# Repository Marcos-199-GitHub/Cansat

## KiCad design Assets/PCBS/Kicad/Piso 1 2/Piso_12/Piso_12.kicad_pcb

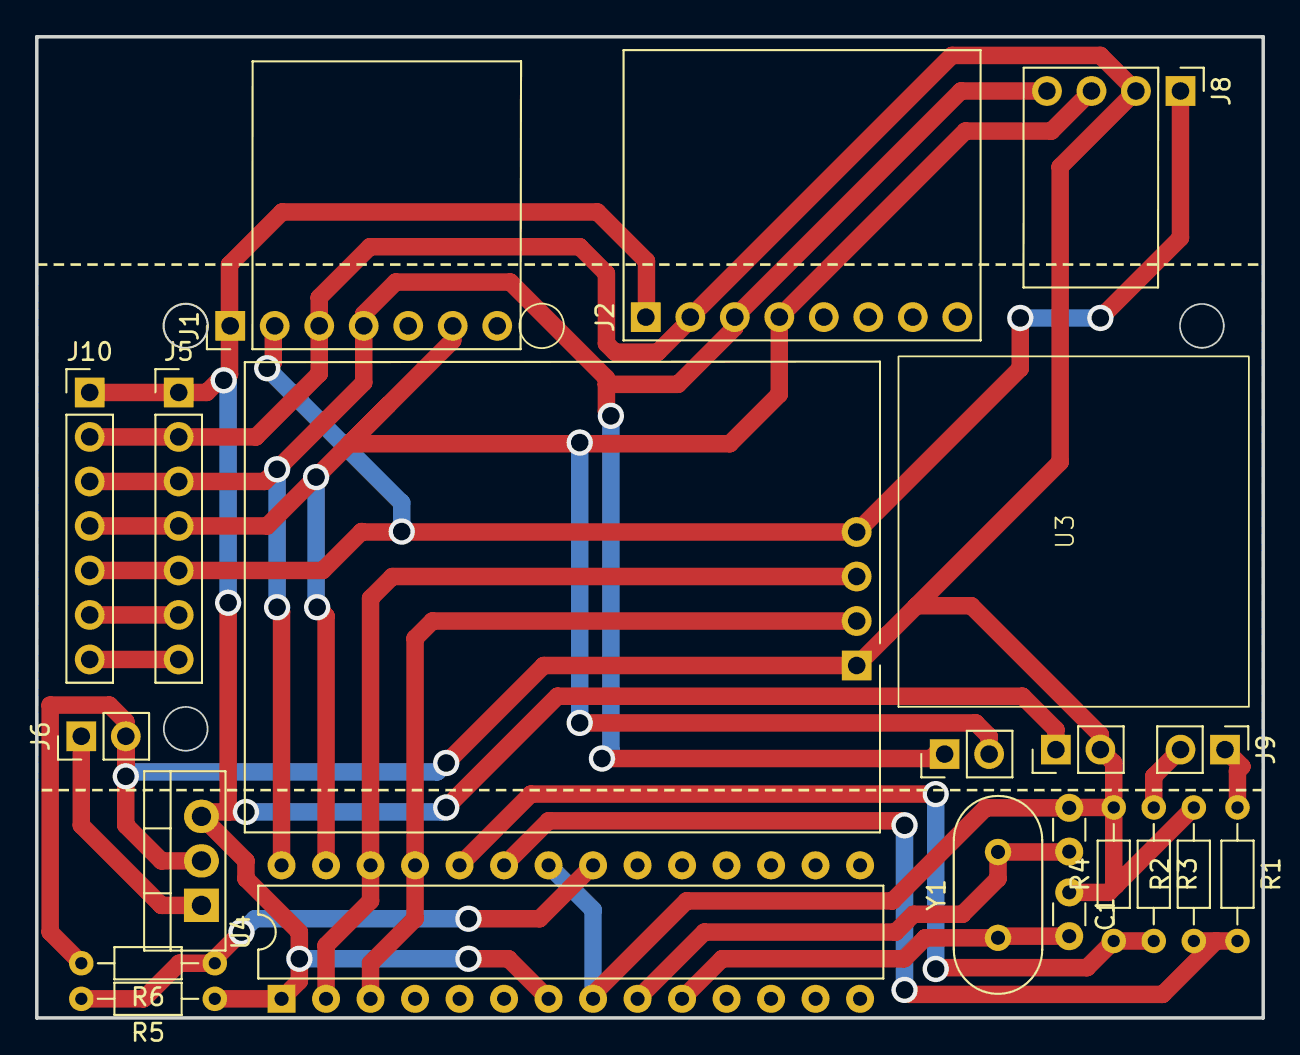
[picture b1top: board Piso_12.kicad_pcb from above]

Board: 2 copper layers, 70.0 x 56.0 mm, 22 parts (0 on the bottom side), 15 nets.

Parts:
C1, C2: 47p; C_Disc_D3.0mm_W1.6mm_P2.50mm
J1: BMP280; PinHeader_1x07_P2.54mm_Vertical
J2: MPU6050; PinHeader_1x08_P2.54mm_Vertical
J3: BMM_PWR; PinHeader_1x02_P2.54mm_Vertical
J4: BMM_DAT; PinHeader_1x02_P2.54mm_Vertical
J5: Output; PinHeader_1x07_P2.54mm_Vertical
J6: BAT; PinHeader_1x02_P2.54mm_Vertical
J7: GPS; GPS Neo-6M
J8: SHT30
J9: EXT; PinHeader_1x02_P2.54mm_Vertical
J10: Input; PinHeader_1x07_P2.54mm_Vertical
R1, R2, R3, R4, R5, R6: R; R_Axial_DIN0204_L3.6mm_D1.6mm_P7.62mm_Horizontal
U1: LM7805_TO220; TO-220-3_Vertical
U3: BMM150
U4: ATmega328P-P; DIP-28_W7.62mm
Y1: Crystal; Crystal_HC18-U_Vertical

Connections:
/3Vo: J1.2, J5.5, J7.4, J8.1, J10.5
/ADC2: R1.2, R2.1, U4.23 (PC0)
/ADC3: R3.2, R4.1, U4.24 (PC1)
/AREF: R5.2, R6.1, U4.21 (AREF)
/BAT: J9.1, R1.1
/GND: C1.1, C2.1, J1.3, J2.2, J3.2, J5.2, J6.2, J7.1, J8.2, J10.2, R2.2, R4.2, R6.2, U1.2 (GND), U4.8 (GND), U4.22 (GND)
/RX: J7.3, U4.2 (PD0)
/SCL: J1.4, J2.3, J4.1, J5.3, J8.4, J10.3, U4.28 (PC5)
/SDA: J1.6, J2.4, J4.2, J5.4, J8.3, J10.4, U4.27 (PC4)
/SHUNT: J9.2, R3.1
/TX: J7.2, U4.3 (PD1)
/VBAT: J6.1, U1.1 (VI)
/VCC: J1.1, J2.1, J3.1, J5.1, J10.1, R5.1, U1.3 (VO), U4.1 (~RESET/PC6), U4.7 (VCC)
unnamed: C2.2, U4.9 (XTAL1/PB6), Y1.2
unnamed: C1.2, U4.10 (XTAL2/PB7), Y1.1

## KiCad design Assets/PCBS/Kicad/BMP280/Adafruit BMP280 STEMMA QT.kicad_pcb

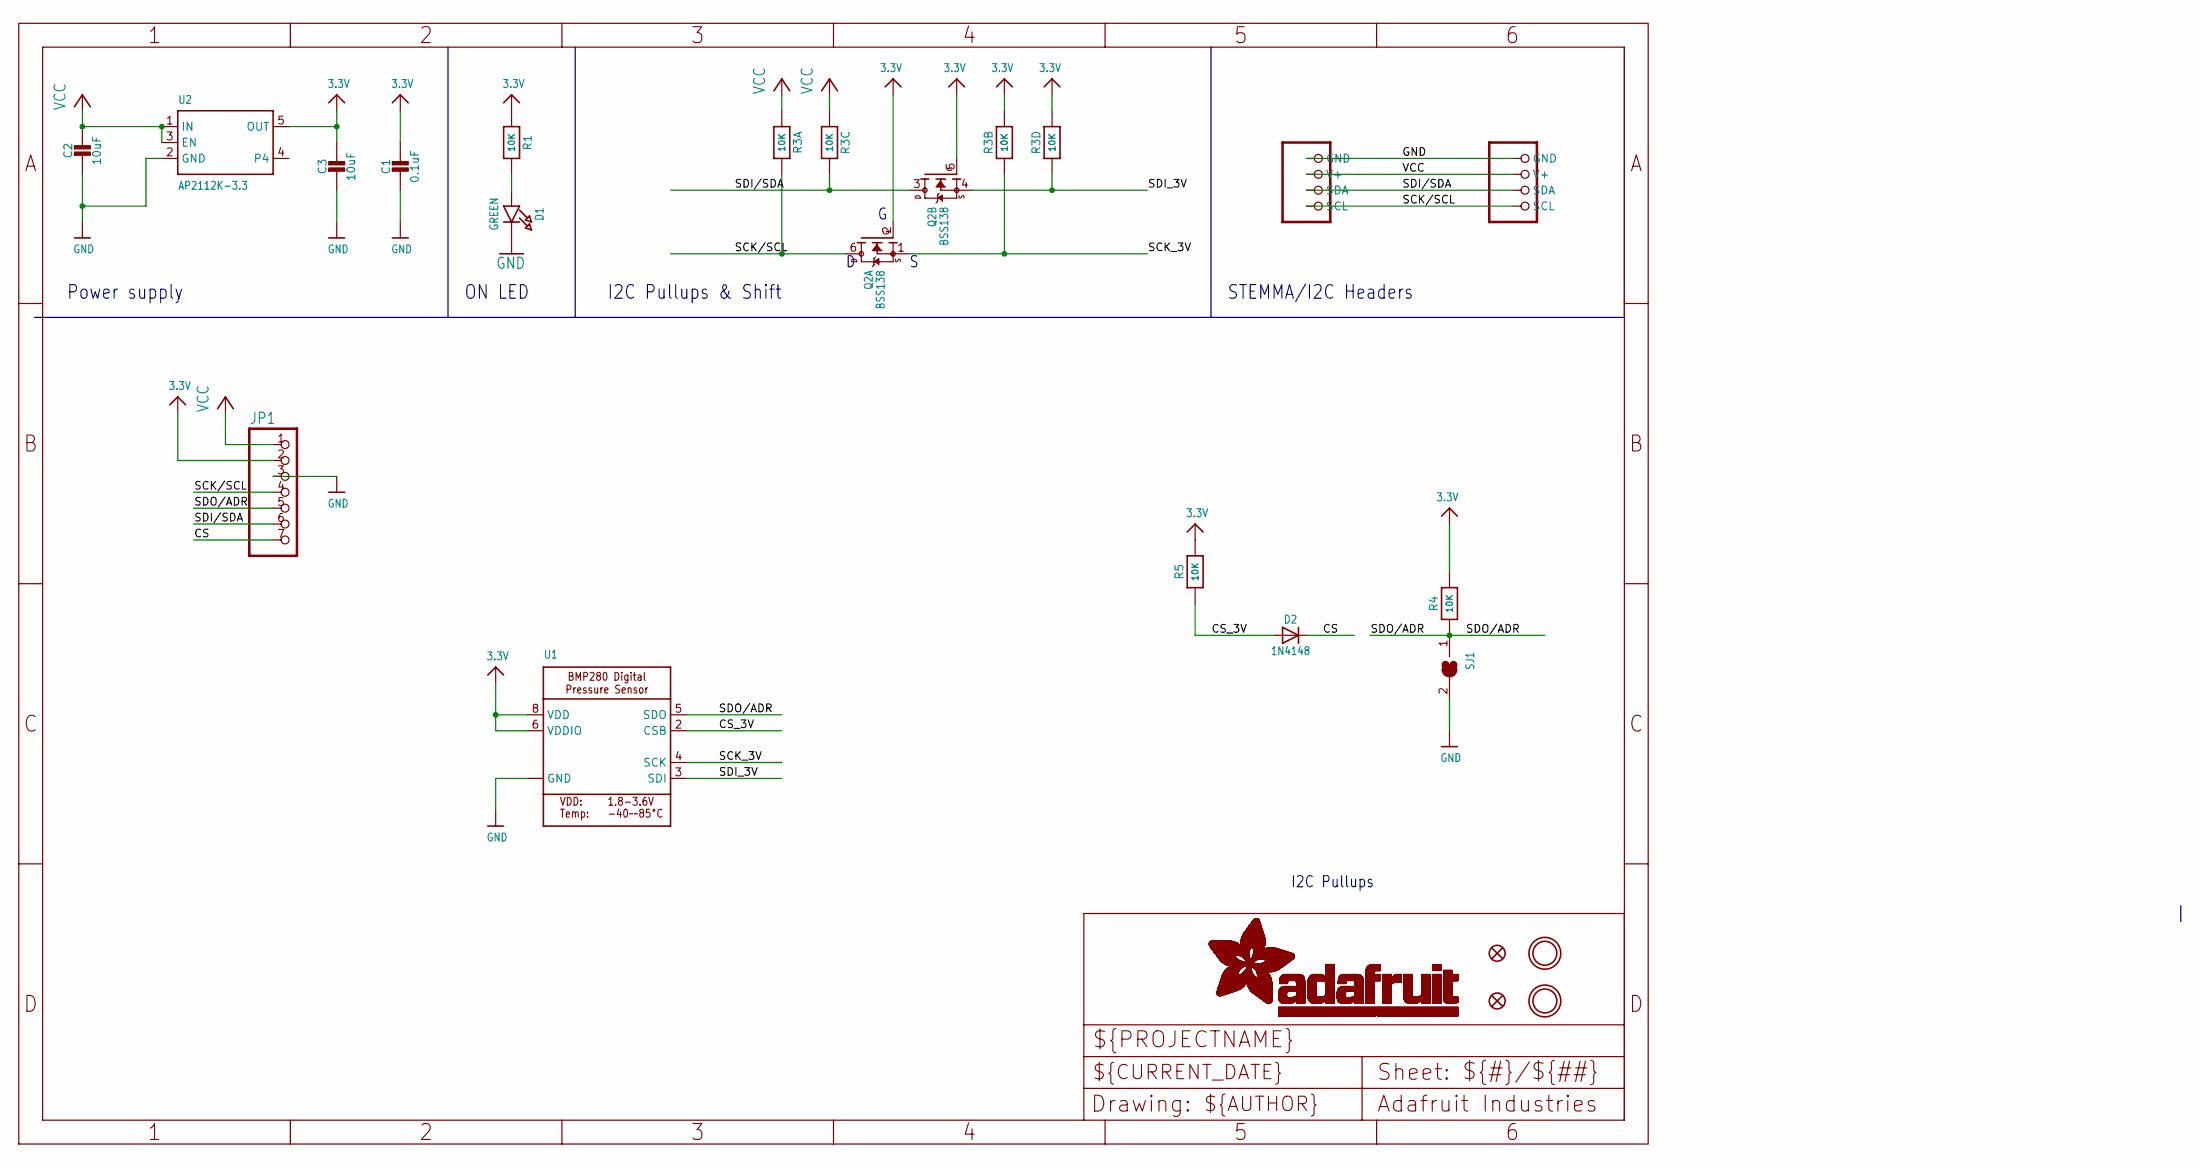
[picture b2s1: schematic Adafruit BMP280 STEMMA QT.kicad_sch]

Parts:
C1: 0.1uF; 0603-NO
C2, C3: 10uF; 0805-NO
CONN3, CONN4: STEMMA_I2C_QT; JST_SH4
D1: GREEN; CHIPLED_0603_NOOUTLINE
D2: 1N4148; SOD-323
FID3, FID4: FIDUCIAL_1MM
JP1: HEADER-1X770MIL; 1X07_ROUND_70
Q2: BSS138; SOT363
R1, R4, R5: 10K; 0603-NO
R3: 10K; RESPACK_4X0603
SJ1: SOLDERJUMPER; SOLDERJUMPER_ARROW_NOPASTE
U1: BMP280_COMBO; BMX280_COMBO
U2: AP2112K-3.3; SOT23-5
U$1, U$17: MOUNTINGHOLE2.5; MOUNTINGHOLE_2.5_PLATED

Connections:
3.3V: C1.1, C3.1, JP1.2, Q2.2 (G), Q2.5 (G), R1.1, R3.2 (1), R3.4 (1), R4.2, R5.2, U1.6 (VDDIO), U1.8 (VDD), U2.5 (OUT)
CS: D2.C, JP1.7
CS_3V: D2.A, R5.1, U1.2 (CSB)
GND: C1.2, C2.2, C3.2, CONN3.1 (GND), CONN4.1 (GND), D1.C, JP1.3, SJ1.2, U1.1 (GND), U1.7 (GND), U2.2 (GND)
unnamed: D1.A, R1.2
SCK/SCL: CONN3.4 (SCL), CONN4.4 (SCL), JP1.4, Q2.6 (D), R3.8 (2)
SCK_3V: Q2.1 (S), R3.7 (2), U1.4 (SCK)
SDI/SDA: CONN3.3 (SDA), CONN4.3 (SDA), JP1.6, Q2.3 (D), R3.6 (2)
SDI_3V: Q2.4 (S), R3.5 (2), U1.3 (SDI)
SDO/ADR: JP1.5, R4.1, SJ1.1, U1.5 (SDO)
VCC: C2.1, CONN3.2 (V+), CONN4.2 (V+), JP1.1, R3.1, R3.3 (1), U2.1 (IN), U2.3 (EN)

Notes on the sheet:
I2C Pullups
I2C Pullups & Shift
STEMMA/I2C Headers
ON LED
Power supply

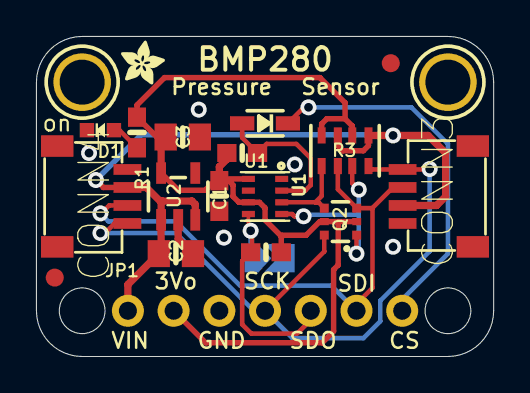
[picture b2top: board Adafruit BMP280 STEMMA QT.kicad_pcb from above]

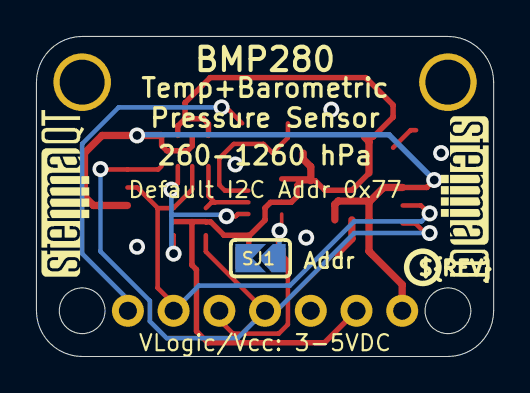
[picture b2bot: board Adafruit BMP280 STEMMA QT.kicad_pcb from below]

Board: 2 copper layers, 25.4 x 17.8 mm, 26 parts (4 on the bottom side), 11 nets.

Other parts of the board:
@HOLE0, @HOLE1: (no value)
U$4: ADAFRUIT_2.5MM
U$25: PCBFEAT-REV-040
U$30, U$31: STEMMAQT

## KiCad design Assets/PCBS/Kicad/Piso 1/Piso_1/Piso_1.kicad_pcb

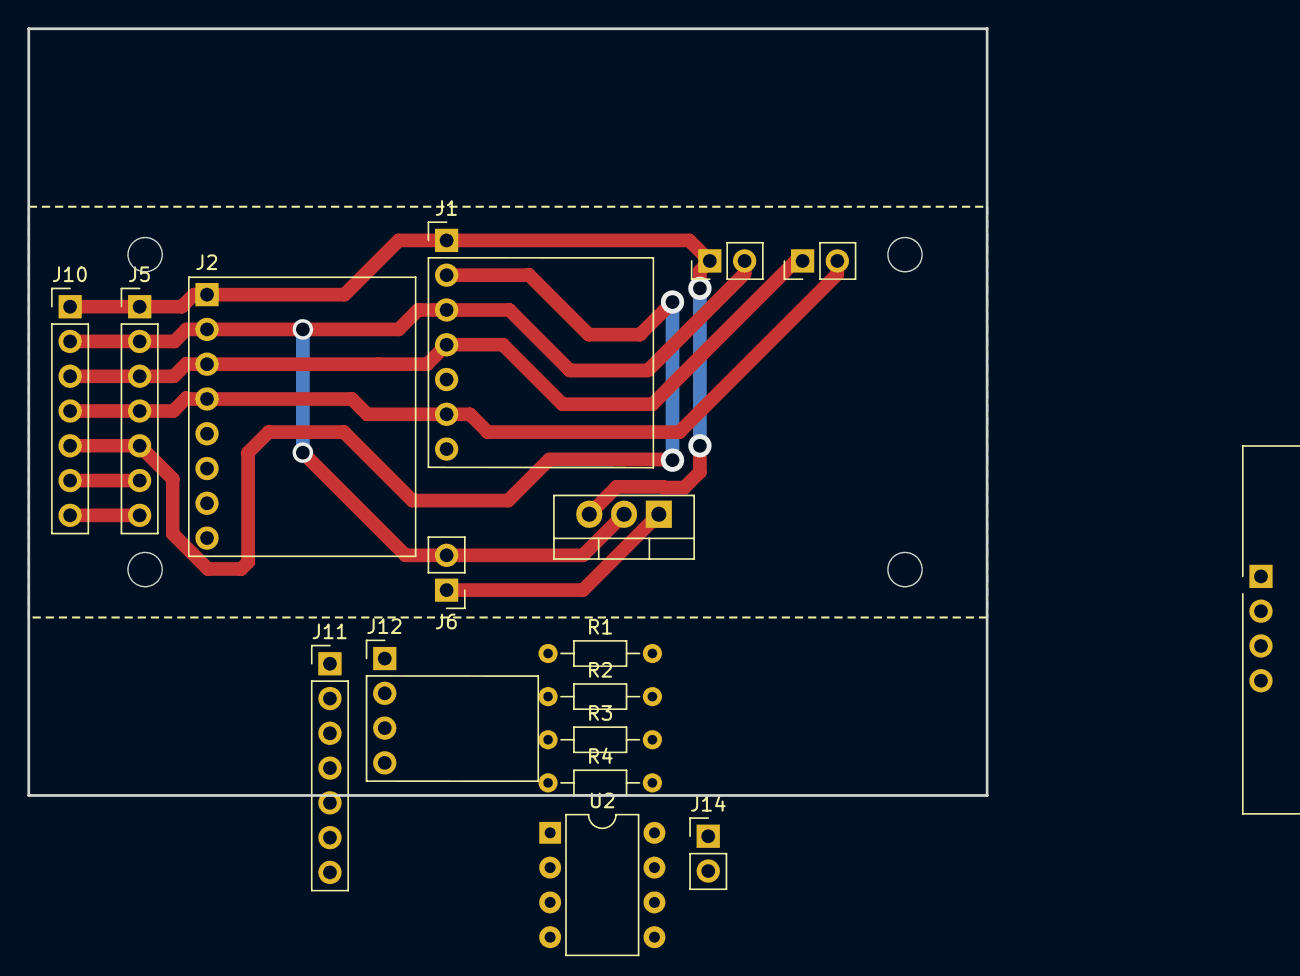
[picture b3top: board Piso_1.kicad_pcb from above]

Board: 2 copper layers, 70.0 x 56.0 mm, 17 parts (0 on the bottom side), 18 nets.

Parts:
J1: BMP280; PinHeader_1x07_P2.54mm_Vertical
J2: MPU6050; PinHeader_1x08_P2.54mm_Vertical
J3: BMM_PWR; PinHeader_1x02_P2.54mm_Vertical
J4: BMM_DAT; PinHeader_1x02_P2.54mm_Vertical
J5: Output; PinHeader_1x07_P2.54mm_Vertical
J6: BAT; PinHeader_1x02_P2.54mm_Vertical
J10: Input; PinHeader_1x07_P2.54mm_Vertical
J11: INPUT_PISO_1; PinHeader_1x07_P2.54mm_Vertical
J12: SHT30
J13: GPS; GPS Neo-6M
J14: EXT; PinHeader_1x02_P2.54mm_Vertical
R1, R2, R3, R4: R; R_Axial_DIN0204_L3.6mm_D1.6mm_P7.62mm_Horizontal
U1: LM7805_TO220; TO-220-3_Vertical
U2: ATtiny45-20P; DIP-8_W7.62mm

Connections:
/3Vo: J1.2, J5.5, J10.5
/BMP/ADC2: R3.2, R4.1, U2.3 (XTAL2/PB4)
/BMP/ADC3: R1.2, R2.1, U2.2 (XTAL1/PB3)
/BMP/BAT: J14.1, R3.1
/BMP/GND: J11.2, J12.2, J13.1, R2.2, R4.2, U2.4 (GND)
/BMP/RX: J11.6, J13.3
/BMP/SCL: J11.3, J12.4, U2.7 (PB2)
/BMP/SDA: J11.4, J12.3, U2.5 (AREF/PB0)
/BMP/SHUNT: J14.2, R1.1
/BMP/TX: J11.7, J13.2
/BMP/VCC3: J11.5, J12.1, J13.4, U2.1 (~RESET/PB5), U2.8 (VCC)
/GND: J1.3, J2.2, J3.2, J5.2, J6.2, J10.2, U1.2 (GND)
/RX: J5.6, J10.6
/SCL: J1.4, J2.3, J4.1, J5.3, J10.3
/SDA: J1.6, J2.4, J4.2, J5.4, J10.4
/TX: J5.7, J10.7
/VBAT: J6.1, U1.1 (VI)
/VCC: J1.1, J2.1, J3.1, J5.1, J10.1, U1.3 (VO)

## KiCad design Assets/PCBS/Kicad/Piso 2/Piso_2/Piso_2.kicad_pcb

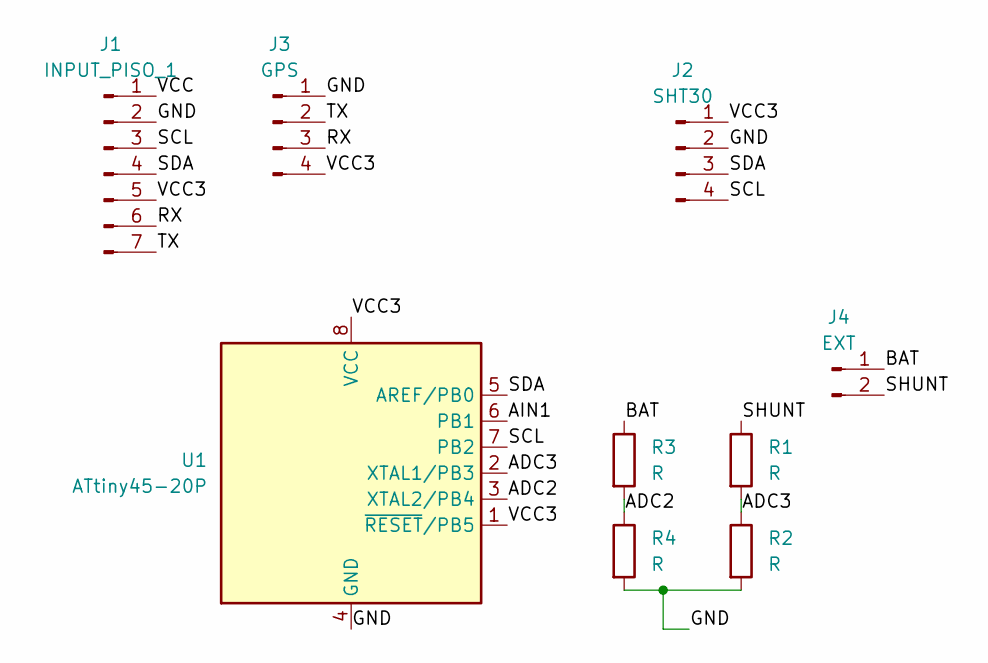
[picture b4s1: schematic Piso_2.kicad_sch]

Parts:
J1: INPUT_PISO_1; PinHeader_1x07_P2.54mm_Vertical
J2: SHT30; PinHeader_1x04_P2.54mm_Vertical
J3: GPS; PinHeader_1x04_P2.54mm_Vertical
J4: EXT; PinHeader_1x02_P2.54mm_Vertical
R1, R2, R3, R4: R; R_Axial_DIN0204_L3.6mm_D1.6mm_P7.62mm_Horizontal
U1: ATtiny45-20P; DIP-8_W7.62mm

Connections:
/ADC2: R3.2, R4.1, U1.3 (XTAL2/PB4)
/ADC3: R1.2, R2.1, U1.2 (XTAL1/PB3)
/AIN1: U1.6 (PB1)
/BAT: J4.1, R3.1
/GND: J1.2, J2.2, J3.1, R2.2, R4.2, U1.4 (GND)
/RX: J1.6, J3.3
/SCL: J1.3, J2.4, U1.7 (PB2)
/SDA: J1.4, J2.3, U1.5 (AREF/PB0)
/SHUNT: J4.2, R1.1
/TX: J1.7, J3.2
/VCC: J1.1
/VCC3: J1.5, J2.1, J3.4, U1.1 (~RESET/PB5), U1.8 (VCC)

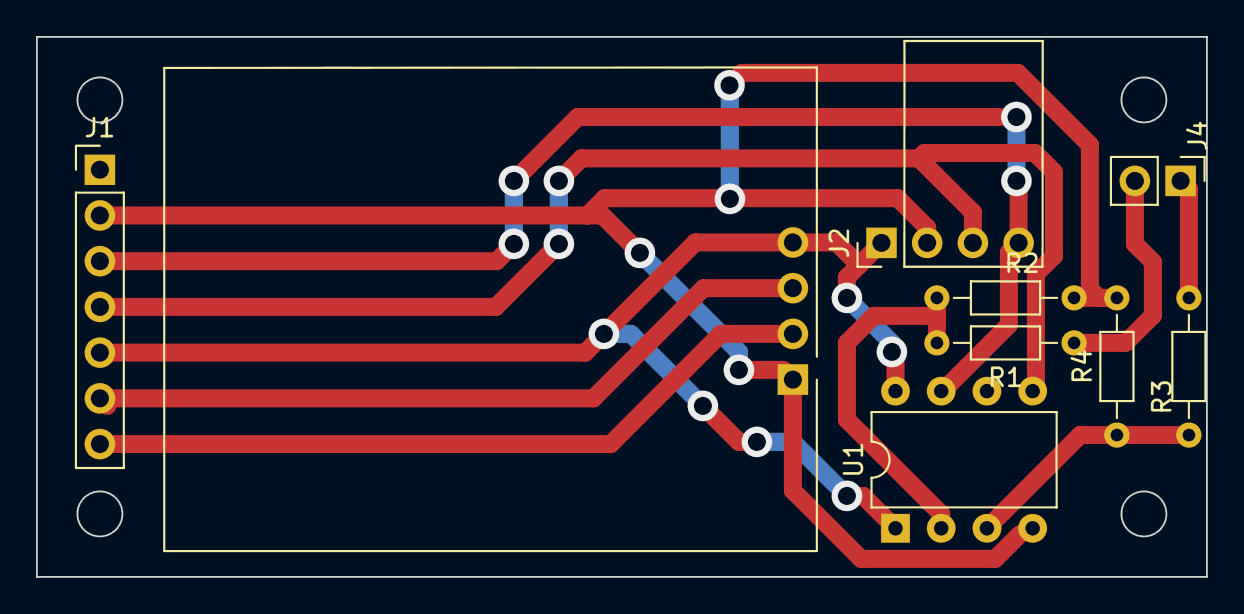
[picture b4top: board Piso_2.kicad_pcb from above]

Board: 2 copper layers, 65.0 x 30.0 mm, 9 parts (0 on the bottom side), 10 nets.

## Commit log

2023-03-20 Ya sirve el serial fisico
2023-03-20 animacion
2023-03-24 Codigo de Raspberry
2023-03-24 Codigo de Raspberry
    Codigo de RFM69
2023-04-10 bug fix
2023-04-11 correcciones aplicadas
2023-05-15 New BMM submodule
2023-05-15 Nuevo submodulo del BMM
2023-05-15 Submodule branch changed
    Cambie el branch porque este si tiene el codigo del BMM150 en python
2023-05-17 LCD
    El programa imprime datos al LCD
2023-05-17 Comentarios
2023-05-17 BMM funciona
2023-05-18 Fuente del LCD y comando de camara
2023-05-18 RFM69 en proceso Nuevos archivos para trabajar el RFM69 y el archivo todo.py ya tiene los comandos de camara (en el commit anterior me falto agregarlo)
2023-05-18 Modelos de Solid
    Modelos para trabajar en solidworks, .step y .stl
2023-05-18 El todo.py envia por RF
2023-05-18 Mensaje por RF truncado a 60 bytes
2023-05-18 Port de micropython a C
    Port de la libreria adafruit_RFM69 de micropython a c++, aun faltan un par de funciones
2023-05-21 RFM Send Funciona
    Ya pude enviar un paquete desde la base al cansat y el cansat lo recibe, aun falta que la base pueda recibir datos
2023-05-21 El Receptor ya recibe !! :100:
    Algunos registros no coincidian, en particular 0x38 (PAYLOAD_LENGTH) estaba en 0, lo que significa que el maximo tamaño de lectura era 0.
    Tambien implemente los DIO para visualizar con leds lo que ocurre.
2023-05-21 Acomodando
2023-05-21 Acomodado X2 :apple:
2023-05-24 Port de la libreria de RFM a PIC
    En proceso, faltan los timers, el usb funciona
2023-05-24 Nueva carpeta de graficas en python
2023-05-27 ver imagen por serial
    Hay un codigo (CamaraCansat) que tiene una casilla de "Por_serial" para elegir si la imagen la tomara del serial o de un archivo bin. Tomando la imagen del archivo bin funciona bien, pero tomandola p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
    Tambien se agregaron archivos .meta eso es de unity
2023-05-31 No mucho
2023-06-04 paracaidas
2023-06-06 Foto
2023-06-06 El PIC ya no utiliza timer
2023-06-07 Mecanismo para probar la caida con un dron
2023-06-25 Literatura para 9DOF
2023-06-25 Camara con python
2023-06-25 Camara Integration
2023-06-29 Infomacion para los IMU y calibracion en proceso
2023-06-29 Calibracion lista
2023-06-29 Fusion de sensores
    Un PDF con mas informacion y en el codigo la implementacion de yaw,pitch,roll para los tres sensores, al igual que su fusion con un filtro complementario
2023-06-29 Implementacion del filtro Kalman en proceso
2023-06-29 Se pueden guardar los datos de calibracion
    Tambien cambie todo lo relacionado a la fusion de los sensores y los filtros a otro modulo
2023-06-30 Acelerometro Calibrado
    Primer intento de obtener la matriz de calibracion del acelerometro, da resultados regulares, quizas se pueda mejorar
2023-07-01 Correcciones :cactus:
2023-07-01 El cable a tierra con PIC ya recibe. Cambie el reloj a 20Mhz
2023-07-01 Nuevo submodulo requerido para el filtro de los IMU
2023-07-01 Modelo del conversor TTL
2023-07-02 El cable a tierra con PIC ya esta terminado. :sunglasses:
    Aun se pueden añadir cosas, pero ya cumple su funcion de recibir datos y mandarlos al puerto serial para procesarse.
2023-07-19 Primer test para determinar angulos de rotacion
2023-07-21 nueva interfaz chingona
2023-08-09 Modulo de camara
2023-08-10 Modulo para comprimir imagenes
2023-08-11 2 decimales en los datos Entre otras cosas
2023-08-11 Test de los datos
2023-08-11 Borre archivos viejos
2023-08-11 Mejora de velocidad de recepcion
    Pase de 0.5 kb/s a 260 kb/s
2023-08-11 Datos de velocidad de envio
2023-08-13 Incorpore GPS y reduje tiempo de envio Cambie el formato de un diccionario con llave/valor, a solo una lista de valores con un orden establecido Tambien quite los datos del display por que reducian v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
2023-08-16 Ya se puede enviar foto, pero es muy lento, aun falta compresion
2023-08-16 Prueba de la recepcion de imagen en python :snake:
2023-08-16 La camara ya funciona en unity
    Tambien puse otra escena donde voy a hacer pruebas de caida libre.
    Y tambien cambie algunas cosas del formato de los datos.
    Las imagenes se guardan en formato jpg, pero no se como funcione lo de mostrarla en unity
2023-08-16 Ya funciona la compresion, solo es cuestion de moverle a los parametros
2023-08-17 Sin threads
2023-08-17 Threads
2023-08-30 ya deberia de poder recibir datos e imagen y mostrarla
2023-08-30 ahora en jpg
2023-09-03 graficas agregadas
2023-09-04 mejoras
2023-09-06 prueba 1
2023-09-06 fixed
2023-09-07 Yikes
2023-09-08 Puerto como variable publica
2023-09-08 Camara funciona
2023-09-10 Nuevo diseño del CanSat
    Excelente :diamond_shape_with_a_dot_inside:
2023-09-11 Retraccion de las patas del cansat
    Aun no esta terminado, pero la idea general ya esta
2023-09-12 Io no fui
2023-09-13 thread implementado
2023-09-29 thread corregido
2023-10-15 Mejoras Removi el LCD hasta nuevo aviso El programa ya no se acaba si algun sensor no funciona Cada vez que inicia, guarda la fecha y hora en el data.log
2023-10-17 More reliable
2023-10-22 Cansat 2.0
    Ahora solo tiene un PCB, donde estan todos los sensores, el GPS, un ATMEGA328 para servir de ADC y transmitir los datos del GPS, todo por I2C. Pasamos de un RFM69 a usar un XBEE para la transmision R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
2023-11-08 Cambios a los PCB
2024-01-04 Modelos Finales
2024-12-10 brujula
